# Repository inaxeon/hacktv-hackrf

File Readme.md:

# HackTV "HackDAC"

This repository is a fork of the HackRF project which contains modified firmware and PCB files for the HackDAC.

# What is it?

HackDAC is an add-on board for the HackRF One intended to provide a broadcast quality baseband video and audio output for HackTV. HackDAC was developed to address a number of frustrations of HackTV users and developers. Firstly, the output of the HackRF is quite noisy, to the extent that it’s visible when viewing television signals generated by HackTV. Secondly it is sometimes more desirable to work with baseband video signals, particularly with devices which do not have an RF input.

# Why is it bristling with trimmable inductors? That looks rather dated!

Well yes, it is. For anybody wanting to design a device which has an analogue video output there are certainly more than a few types of chip for the job, however these (to the best of our current knowledge) are all "consumer video encoder" chips. While these devices are plentiful, inexpensive and produce good quality signals using just a single chip with a few passives at the output, unfortunately they do all of the sync generation and chrominance encoding internally, limiting the output typically to just PAL and NTSC (and SECAM in some rare cases).

HackTV on the other hand is a fully software defined TV transmitter which does not want the output hardware doing anything clever for it – this is why it is able to generate a massive range of TV signals, some quite obscure.

Ultimately HackTV wants a high-quality arbitrary video signal generator as its output and sadly there is no commercial reason for such a thing to exist, beyond analogue video test equipment, very little of which is designed or sold today.

In 2022 Danish Entrepreneur Karsten Hansen dumped 4 gigabytes of engineering materials from Philips TV & Test Equipment into a github repository (intellectual property he personally came to own). Contained within the repository was detailed information about how to build and calibrate a very high-quality arbitrary video signal generator circuit first used in the Philips PM5655. This circuit became the basis of "HackDAC Alpha" – the current design.

Unfortunately it's quite difficult to build, and calibrating it takes some practice, not to mention some specialised test equipment. Longer term the project will have to wave goodbye to this circuit and move to a digital oversampling solution however it is important for the time being, firstly because it works and proves the concept, secondly because its performance is exceptional and provides a benchmark for any future designs.

# Firmware details

<details>

Contained within this repository is a modified version of the HackRF One's firmware which is required to support the HackDAC. It is the explicit intention that this firmware must retain all functionality of the HackRF One and full compatibility with libhackrf. As such any defects should be regarded as bugs and reported here.

Note that the HackDAC firmware increases the USB data buffer from 32KiB to the maximum 64KiB. This may effect latency when using the HackRF for low-bandwidth non-HackTV applications.

</details>

# Hardware details

<details>

## Design

The most prominent feature of the present design is the filter after the DAC. It is a full analogue reconstruction filter which corrects its own errors and allows the DAC to run at 1x sample rate. Such a filter is required when attaching to the HackRF as the maximum sample rate is about 20 MHz, not enough even for 2x oversampling.

During operation the HackRF's CPLD is re-programmed to emit data from the normally unused BANK2_AUX header, instead of the on-board analogue frontend. Realisation of video signals is performed by the 16-bit AD768 from Analogue Devices, the very same DAC originally used by Philips. It's an old chip with quite a price tag but remains in production and still has respectable performance even by todays' standards. Replacement of it with a newer, low-cost device was considered however it was found this would impose a number of compromises and require significant alterations to the design, none of which the project is particularly willing to accept at this time. Nonetheless in future it will have to be abandoned due to its high cost.

Video resolution is limited to 15-bit, as the 16th bit from the CPU is used for the Sync output.

Jitter was a particular difficulty during the development of HackDAC. The root cause of the problem is the HackRF's Si5351c/a PLL; a low-quality consumer chip with poor jitter characteristics, even when using the most optimum divisor ratios. To work around the problem, when running in baseband video mode the HackDAC firmware re-programs the Si5351 to act as a clock buffer, disabling its PLL entirely. HackDAC then clocks the Si5351 from its on-board 27 MHz TCXO, providing a stable, extremely low jitter to clock to the HackRF's CPLD and MCU. 

Audio is handled by a PCM5102 DAC run at a sample rate of 210.9 KHz, the 13.5 MHz video sample rate divided by 64. This ratio arises from interleaved transfers of 16KiB video data, followed by 512B of audio data to the HackRF, a scheme which was found to be efficient and reliable.

When a HackDAC is attached to the HackRF it should remain powered down, and not in any way impair non-HackTV related usage of it (even with standard firmware). Any issues in this scenario should be reported as bugs.

## Variable inductor construction

HackDAC uses proprietary Philips inductors in its output filter. Original parts are not purchasable from any source today however they can be recreated using inductor kits. To achieve correct characteristics the following instructions must be exactly followed.

All inductors are made from the WELCO SBK-71S kit *with* the optional SBK-CF1 ferrite cup. Bobbins must be wound with 0.1mm copper wire *using only the bottom half of the bobbon* It is important the top half is left free of windings. Once the bobbins are wound the windings must be varnished to ensure they do not move.

Single winding types:
* 4008 100 09500: 1pcs per board. 42.5 turns. Target inductance: 8.0-15.0uH
* 4008 100 09760: 2pcs per board. 9.5 turns. Target inductance: 0.5-1.0uH
* 4008 100 09750: 3pcs per board. 11.5 turns. Target inductance: 0.8-1.8uH

A single wire is wound counter-clockwise between pins 1 and 4. All turn counts are given including the extra half turn to reach the opposing pin. i.e. 9.5T = 9 full turns from pin 1, plus the extra half turn to reach pin 4.

Double winding types:
* 4008 100 09510: 1pcs per board. 10.5 turns. Target inductance: 0.7-1.2uH
* 4008 100 09770: 1pcs per board. 16.5 turns. Target inductance: 1.3-3.0uH

Two separate wires are wound counter-clockwise (both in the same direction) One starting at pin 1 ending at 4, and another starting at pin 2 ending at 5. Both must be of an identical number of turns. Verification of target inductance must be performed with both windings in parallel.

</details>

# Calibration

<details>

A number of steps are required to calibrate a HackDAC. Below is the method I personally use. I warn that it takes some time to master in practise.

### DC Offset / gain calibration:

Each board has individually calibration DC gain and offset. It is performed using the "hackdac_cal" tool in this repository.

Upon running it with an assembled HackRF/HackDAC the user is given the option to set the output voltage to either -1V, 0V or +1V. Additional keystrokes allow the gain and offset to be adjusted in realtime so to achieve correct voltage as measured on a DMM attached to the HackDAC's video output terminated at 75Ω.

Once the procedure is completed the calibrations can be saved into nonvolatile memory contained within the calibration DAC on the HackDAC board.

### Low pass filter calibration

Test setup:

For this procedure the HackDAC must be connected to a baseband VNA using the A/R MAG input configuration. The procedure is possible with an RF VNA with a built-in S-Parameter test set however the test cable setup will differ and you most likely won't be able to accurately measure frequency response or group delay accurately below 1 MHz.

Firstly the low pass filter must be adjusted:

* L9: 10 MHz
* L8: 8.05 MHz
* L7: 16.8 MHz

Resonant frequencies can be observed in the stopband as per this plot:

### Group delay equaliser calibration

In this procedure the VNA will need to be set the A/R DELAY measurement. L3, L4, L5 and L6 are adjusted to keep Tg deviation within 5ns as per this diagram:

In practise this is rather difficult to do and somewhat overkill for any realistic application today. You may find you can get it within 20ns which is still more than good enough.

### SIN X/X correction calibration

To calibrate the SIN X/X corrector HackTV must be set to generate the SIN X/X test signal. L10 and C39 must be adjusted to achieve symmetry of the SIN X/X test signal as below:

Now start HackTV with the "Pulse & Bar" test signal. Check the 2T pulse is symmetrical as below. Ajust group delay & SIN X/X as necessary to resolve any issues.

### Final check with vectorscope

Lastly if you have an accurate/calibrated vectorscope to hand it is useful for validating the previous adjustments. Start HackTV with the 75% EBU colour bars test signal and verify the output on a vectorscope matches the below:

Colours should fall exactly in the 75% boxes in the graticule, traces between vectors should be perfectly straight. Examples of problems likely to be seen are differential phase errors and incorrect colour subcarrier amplitude. Fine tune the group delay equaliser and SIN X/X correction as necessary to resolve.
</details>

# Specifications

## Video output
* Bandwidth: DC-6 MHz
* Voltage range: 2V pk-pk (+/- 1V)
* Output impedence: 75Ω
* Sample rate: 13.5 MHz (fixed, per CCIR 601)
* Word size: 15-bit

## Sync output
* Output voltage: -1.8V (0v at rest)
* Rise time: 230ns
* Output impedence: 75Ω

## Audio output
* Output voltage: 2.1 V(RMS)
* Sample rate (with video): 210.9 KHz
* Sample rate (standalone): 48 KHz
* Word size: 16-bit

# Schematic

[Can be viewed here](https://github.com/inaxeon/hacktv-hackrf/blob/master/hardware/hackdac-alpha/hackdac-alpha-rev3.pdf).

# How do I obtain one?

While fully open-source HackDACs are produced in small quantities and available to purchase pre-made. Contact me at inaxeon@hotmail.com for more information.

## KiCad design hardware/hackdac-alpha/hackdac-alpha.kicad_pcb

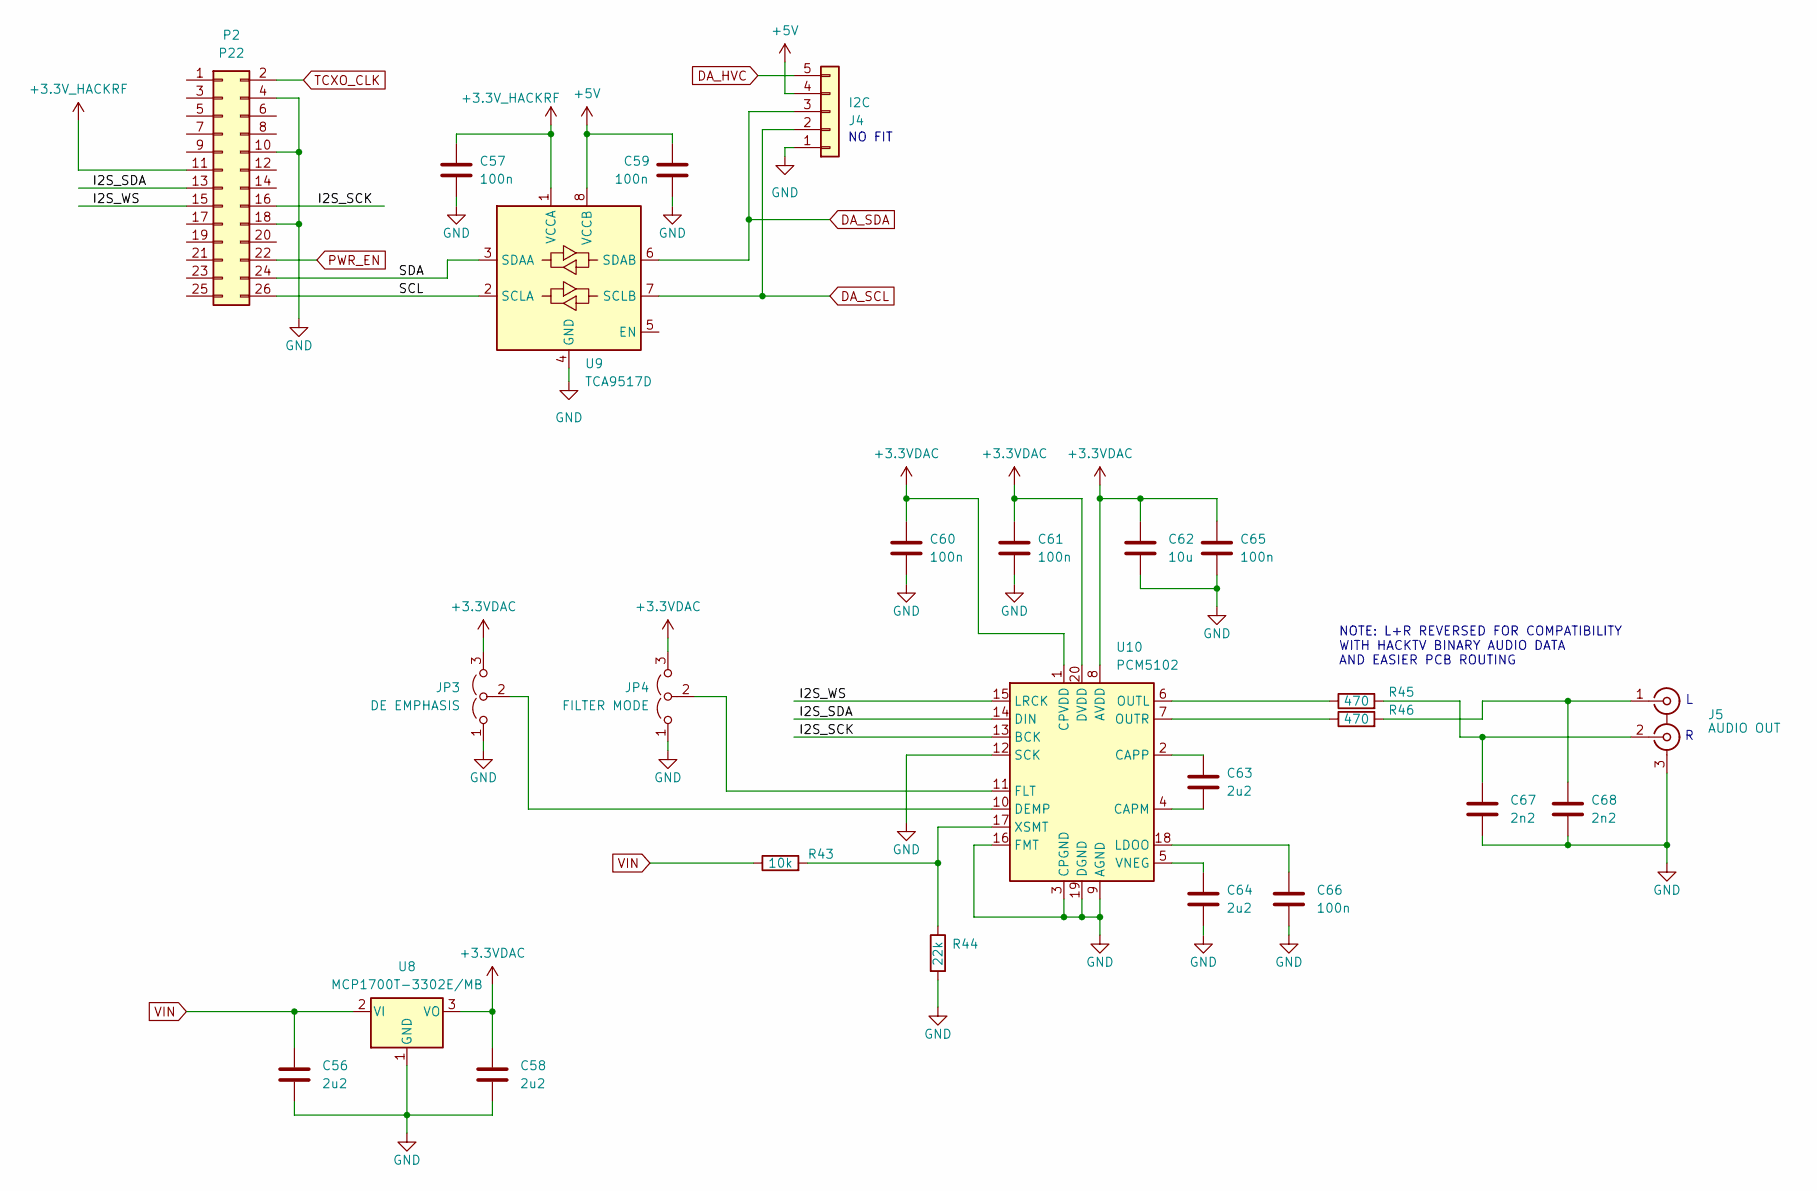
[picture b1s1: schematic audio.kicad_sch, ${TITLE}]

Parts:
C56, C58, C63, C64: 2u2; C_0603_1608Metric
C57, C59, C60, C61, C65, C66: 100n; C_0603_1608Metric
C62: 10u; C_1210_3225Metric
C67, C68: 2n2; C_0603_1608Metric
J4: I2C; Molex_KK-254_AE-6410-05A_1x05_P2.54mm_Vertical
J5: AUDIO OUT; PJRAN2X1U01X
JP3: DE EMPHASIS; SolderJumper-3_P1.3mm_Bridged12_Pad1.0x1.5mm
JP4: FILTER MODE; SolderJumper-3_P1.3mm_Bridged12_Pad1.0x1.5mm
P2: P22; GSG-HEADER-2x13
R43: 10k; R_0603_1608Metric
R44: 22k; R_0603_1608Metric
R45, R46: 470; R_0603_1608Metric
U8: MCP1700T-3302E/MB; SOT-89-3
U9: TCA9517D; SOIC-8_3.9x4.9mm_P1.27mm
U10: PCM5102; TSSOP-20_4.4x6.5mm_P0.65mm

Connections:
+3.3VDAC: C58.1, C60.1, C61.1, C62.1, C65.1, JP3.3 (B), JP4.3 (B), U8.3 (VO), U10.1 (CPVDD), U10.8 (AVDD), U10.20 (DVDD)
+3.3V_HACKRF: C57.1, P2.11, U9.1 (VCCA); also elsewhere on the board
+5V: C59.1, J4.4, U9.8 (VCCB); also elsewhere on the board
/audio/I2S_SCK: P2.16, U10.13 (BCK)
/audio/I2S_SDA: P2.13, U10.14 (DIN)
/audio/I2S_WS: P2.15, U10.15 (LRCK)
/audio/SCL: P2.26, U9.2 (SCLA)
/audio/SDA: P2.24, U9.3 (SDAA)
DA_HVC: J4.5; also elsewhere on the board
DA_SCL: J4.2, U9.7 (SCLB); also elsewhere on the board
DA_SDA: J4.3, U9.6 (SDAB); also elsewhere on the board
GND: C56.2, C57.2, C58.2, C59.2, C60.2, C61.2, C62.2, C64.2, C65.2, C66.2, C67.2, C68.2, J4.1, J5.3 (EXT), JP3.1 (A), JP4.1 (A), P2.4, P2.10, P2.18, R44.2, U8.1 (GND), U9.4 (GND), U10.3 (CPGND), U10.9 (AGND), U10.12 (SCK), U10.16 (FMT), U10.19 (DGND); also elsewhere on the board
unnamed: C68.1, J5.1 (IN1), R46.2
unnamed: C67.1, J5.2 (IN2), R45.2
unnamed: JP3.2 (C), U10.10 (DEMP)
unnamed: JP4.2 (C), U10.11 (FLT)
unnamed: C63.2, U10.4 (CAPM)
unnamed: C63.1, U10.2 (CAPP)
unnamed: C66.1, U10.18 (LDOO)
unnamed: R45.1, U10.6 (OUTL)
unnamed: R46.1, U10.7 (OUTR)
unnamed: C64.1, U10.5 (VNEG)
unnamed: R43.2, R44.1, U10.17 (XSMT)
PWR_EN: P2.22; also elsewhere on the board
TCXO_CLK: P2.2; also elsewhere on the board
VIN: C56.1, R43.1, U8.2 (VI); also elsewhere on the board

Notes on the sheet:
NOTE: L+R REVERSED FOR COMPATIBILITY WITH HACKTV BINARY AUDIO DATA AND EASIER PCB ROUTING
NO FIT

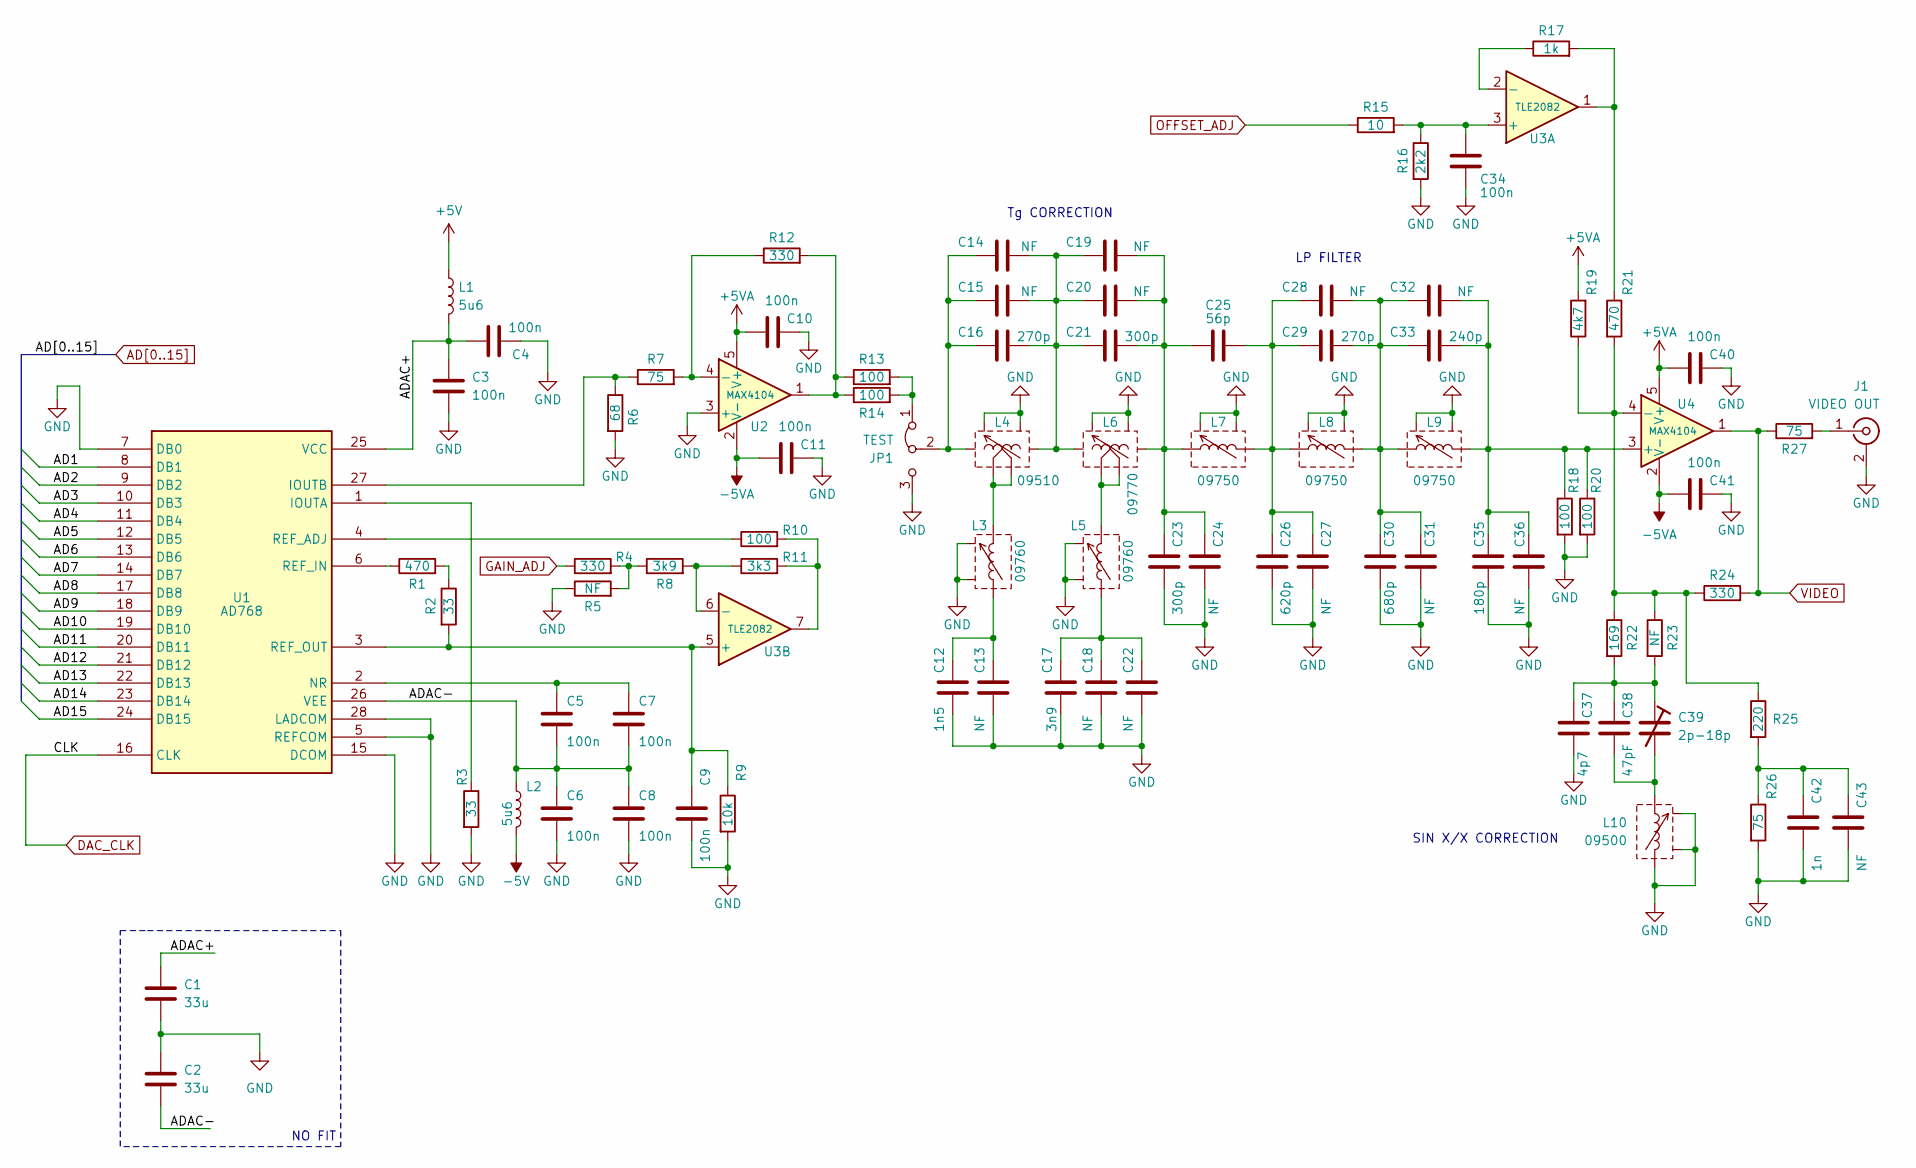
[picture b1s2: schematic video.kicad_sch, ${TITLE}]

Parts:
C1, C2: 33u; C_1210_3225Metric
C3, C4, C5, C6, C7, C8, C9, C10, C11, C34, C40, C41: 100n; C_0603_1608Metric
C12: 1n5; C_0603_1608Metric
C13, C14, C15, C18, C19, C20, C22, C24, C27, C28, C31, C32, C36, C43: NF; C_0603_1608Metric
C16, C29: 270p; C_0603_1608Metric
C17: 3n9; C_0603_1608Metric
C21, C23: 300p; C_0603_1608Metric
C25: 56p; C_0603_1608Metric
C26: 620p; C_0603_1608Metric
C30: 680p; C_0603_1608Metric
C33: 240p; C_0603_1608Metric
C35: 180p; C_0603_1608Metric
C37: 4p7; C_0603_1608Metric
C38: 47pF; C_0603_1608Metric
C39: 2p-18p; BFC2808xxxxx
C42: 1n; C_0603_1608Metric
J1: VIDEO OUT; 731010120
JP1: TEST; PinHeader_1x03_P2.54mm_Vertical
L1, L2: 5u6; L_1210_3225Metric
L3, L5: 09760; NEOSID_7MM
L4: 09510; NEOSID_7MM
L6: 09770; NEOSID_7MM
L7, L8, L9: 09750; NEOSID_7MM
L10: 09500; NEOSID_7MM
R1, R21: 470; R_0603_1608Metric
R2, R3: 33; R_0603_1608Metric
R4, R12, R24: 330; R_0603_1608Metric
R5, R23: NF; R_0603_1608Metric
R6: 68; R_0603_1608Metric
R7, R26, R27: 75; R_0603_1608Metric
R8: 3k9; R_0603_1608Metric
R9: 10k; R_0603_1608Metric
R10, R13, R14, R18, R20: 100; R_0603_1608Metric
R11: 3k3; R_0603_1608Metric
R15: 10; R_0603_1608Metric
R16: 2k2; R_0603_1608Metric
R17: 1k; R_0603_1608Metric
R19: 4k7; R_0603_1608Metric
R22: 169; R_0603_1608Metric
R25: 220; R_0603_1608Metric
U1: AD768; SOIC-28W_7.5x18.7mm_P1.27mm
U2, U4: MAX4104; SOT-23-5
U3: TLE2082; SOIC-8_3.9x4.9mm_P1.27mm

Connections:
+5V: L1.1; also elsewhere on the board
+5VA: C10.1, C40.1, R19.2, U2.5 (V+), U4.5 (V+); also elsewhere on the board
-5V: L2.2; also elsewhere on the board
-5VA: C11.1, C41.1, U2.2 (V-), U4.2 (V-); also elsewhere on the board
/video/ADAC+: C1.1, C3.2, C4.2, L1.2, U1.25 (VCC)
/video/ADAC-: C2.2, C5.2, C6.1, C7.1, C8.1, L2.1, U1.26 (VEE)
AD1: U1.8 (DB1); also elsewhere on the board
AD2: U1.9 (DB2); also elsewhere on the board
AD3: U1.10 (DB3); also elsewhere on the board
AD4: U1.11 (DB4); also elsewhere on the board
AD5: U1.12 (DB5); also elsewhere on the board
AD6: U1.13 (DB6); also elsewhere on the board
AD7: U1.14 (DB7); also elsewhere on the board
AD8: U1.17 (DB8); also elsewhere on the board
AD9: U1.18 (DB9); also elsewhere on the board
AD10: U1.19 (DB10); also elsewhere on the board
AD11: U1.20 (DB11); also elsewhere on the board
AD12: U1.21 (DB12); also elsewhere on the board
AD13: U1.22 (DB13); also elsewhere on the board
AD14: U1.23 (DB14); also elsewhere on the board
AD15: U1.24 (DB15); also elsewhere on the board
DAC_CLK: U1.16 (CLK); also elsewhere on the board
GAIN_ADJ: R4.1; also elsewhere on the board
GND: C1.2, C2.1, C3.1, C4.1, C6.2, C8.2, C9.2, C10.2, C11.2, C12.2, C13.2, C17.2, C18.2, C22.2, C23.2, C24.2, C26.2, C27.2, C30.2, C31.2, C34.2, C35.2, C36.2, C37.2, C40.2, C41.2, C42.2, C43.2, J1.2 (Ext), JP1.3 (B), L3.6, L4.6, L5.6, L6.6, L7.6, L8.6, L9.6, L10.4, L10.6, R3.2, R5.1, R6.2, R9.2, R16.2, R18.2, R20.2, R26.2, U1.5 (REFCOM), U1.7 (DB0), U1.15 (DCOM), U1.28 (LADCOM), U2.3 (+); also elsewhere on the board
unnamed: C12.1, C13.1, L3.4
unnamed: C14.2, C15.2, C16.2, C19.1, C20.1, C21.1, L4.1, L6.5
unnamed: C17.1, C18.1, C22.1, L5.4
unnamed: C19.2, C20.2, C21.2, C23.1, C24.1, C25.1, L6.1, L7.1
unnamed: C25.2, C26.1, C27.1, C28.1, C29.1, L7.4, L8.1
unnamed: C28.2, C29.2, C30.1, C31.1, C32.1, C33.1, L8.4, L9.1
unnamed: C37.1, C38.1, C39.1, R22.2, R23.2
unnamed: C38.2, C39.2, L10.1
unnamed: C42.1, C43.1, R25.2, R26.1
unnamed: J1.1 (In), R27.2
unnamed: JP1.1 (A), R13.2, R14.2
unnamed: C14.1, C15.1, C16.1, JP1.2 (C), L4.5
unnamed: L3.1, L4.2, L4.4
unnamed: L5.1, L6.2, L6.4
unnamed: R1.2, R2.1
unnamed: R4.2, R5.2, R8.1
unnamed: R10.2, R11.2, U3.7
unnamed: R12.2, R13.1, R14.1, U2.1
unnamed: R17.2, R21.1, U3.1
unnamed: R3.1, U1.1 (IOUTA)
unnamed: R6.1, R7.1, U1.27 (IOUTB)
unnamed: C5.1, C7.2, U1.2 (NR)
unnamed: R10.1, U1.4 (REF_ADJ)
unnamed: R1.1, U1.6 (REF_IN)
unnamed: C9.1, R2.2, R9.1, U1.3 (REF_OUT), U3.5 (+)
unnamed: R7.2, R12.1, U2.4 (-)
unnamed: C34.1, R15.2, R16.1, U3.3 (+)
unnamed: R17.1, U3.2 (-)
unnamed: R8.2, R11.1, U3.6 (-)
unnamed: C32.2, C33.2, C35.1, C36.1, L9.4, R18.1, R20.1, U4.3 (+)
unnamed: R19.1, R21.2, R22.1, R23.1, R24.1, R25.1, U4.4 (-)
OFFSET_ADJ: R15.1; also elsewhere on the board
VIDEO: R24.2, R27.1, U4.1; also elsewhere on the board

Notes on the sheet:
LP FILTER
Tg CORRECTION
NO FIT
SIN X/X CORRECTION

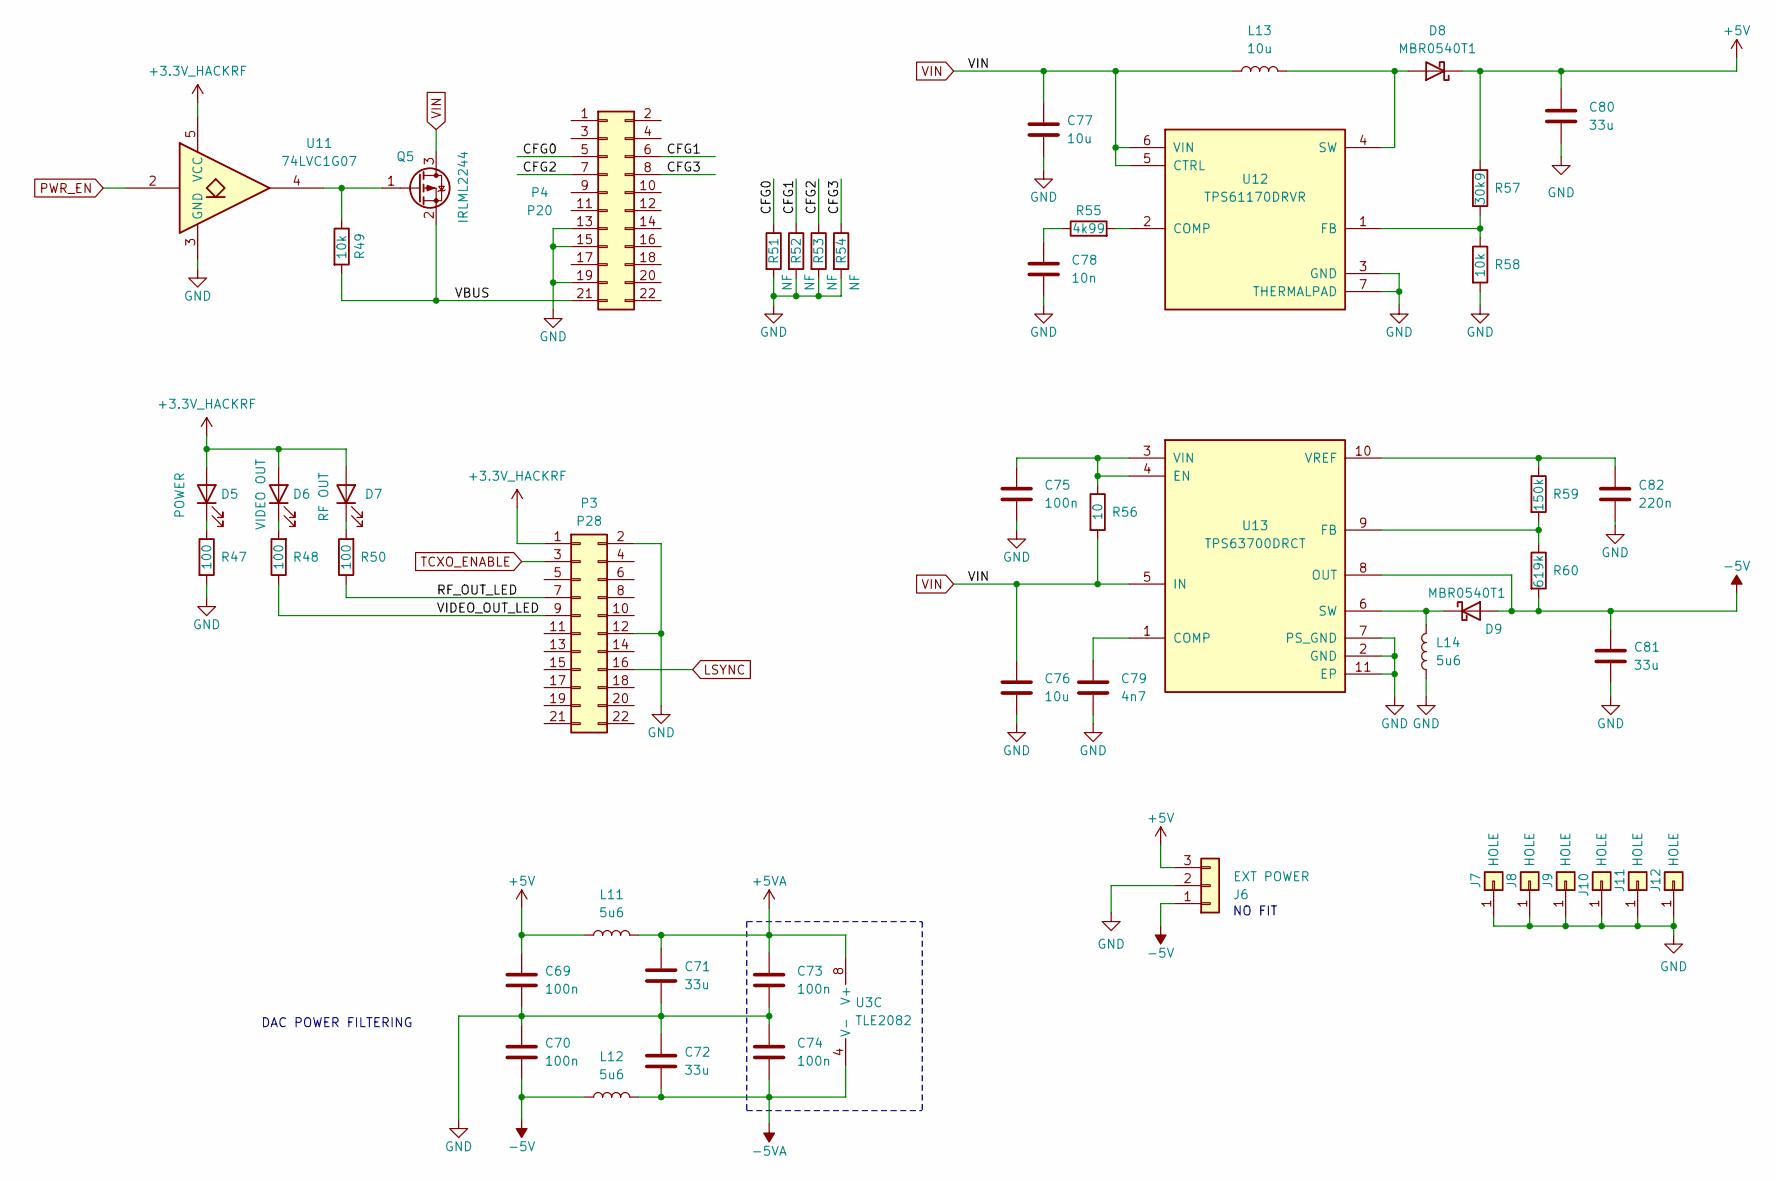
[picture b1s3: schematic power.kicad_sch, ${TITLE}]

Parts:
C69, C70, C73, C74, C75: 100n; C_0603_1608Metric
C71, C72, C80, C81: 33u; C_1210_3225Metric
C76, C77: 10u; C_1210_3225Metric
C78: 10n; C_0603_1608Metric
C79: 4n7; C_0603_1608Metric
C82: 220n; C_0603_1608Metric
D5: POWER; LED_0805_2012Metric
D6: VIDEO OUT; LED_0805_2012Metric
D7: RF OUT; LED_0805_2012Metric
D8, D9: MBR0540T1; D_SOD-123
J6: EXT POWER; Molex_KK-254_AE-6410-03A_1x03_P2.54mm_Vertical
J7, J8, J9, J10, J11, J12: HOLE; GSG-HOLE126MIL-COPPER
L11, L12, L14: 5u6; L_1210_3225Metric
L13: 10u; L_1210_3225Metric
P3: P28; GSG-HEADER-2x11
P4: P20; GSG-HEADER-2x11
Q5: IRLML2244; SOT-23
R47, R48, R50: 100; R_0603_1608Metric
R49, R58: 10k; R_0603_1608Metric
R51, R52, R53, R54: NF; R_0603_1608Metric
R55: 4k99; R_0603_1608Metric
R56: 10; R_0603_1608Metric
R57: 30k9; R_0603_1608Metric
R59: 150k; R_0603_1608Metric
R60: 619k; R_0603_1608Metric
U3: TLE2082; SOIC-8_3.9x4.9mm_P1.27mm
U11: 74LVC1G07; SOT-23-5
U12: TPS61170DRVR; SON65P200X200X80-7N
U13: TPS63700DRCT; VREG_V62_16624-01YE

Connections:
+3.3V_HACKRF: D5.2 (A), D6.2 (A), D7.2 (A), P3.1, U11.5 (VCC); also elsewhere on the board
+5V: C69.1, C80.1, D8.1 (K), J6.3, L11.1, R57.1; also elsewhere on the board
+5VA: C71.1, C73.1, L11.2, U3.8 (V+); also elsewhere on the board
-5V: C70.2, C81.1, D9.2 (A), J6.1, L12.1, R60.2, U13.8 (OUT); also elsewhere on the board
-5VA: C72.2, C74.2, L12.2, U3.4 (V-); also elsewhere on the board
/power/CFG0: P4.5, R51.1
/power/CFG1: P4.6, R52.1
/power/CFG2: P4.7, R53.1
/power/CFG3: P4.8, R54.1
/power/RF_OUT_LED: P3.7, R50.1
/power/VBUS: P4.21, Q5.2 (S), R49.2
/power/VIDEO_OUT_LED: P3.9, R48.1
GND: C69.2, C70.1, C71.2, C72.1, C73.2, C74.1, C75.2, C76.2, C77.2, C78.2, C79.2, C80.2, C81.2, C82.2, J6.2, J7.1, J8.1, J9.1, J10.1, J11.1, J12.1, L14.1, P3.2, P3.12, P4.13, P4.15, P4.19, R47.2, R51.2, R52.2, R53.2, R54.2, R58.2, U11.3 (GND), U12.3 (GND), U12.7 (THERMALPAD), U13.2 (GND), U13.7 (PS_GND), U13.11 (EP); also elsewhere on the board
LSYNC: P3.16; also elsewhere on the board
unnamed: C78.1, R55.1
unnamed: D5.1 (K), R47.1
unnamed: D6.1 (K), R48.2
unnamed: D7.1 (K), R50.2
unnamed: D8.2 (A), L13.2, U12.4 (SW)
unnamed: D9.1 (K), L14.2, U13.6 (SW)
unnamed: Q5.1 (G), R49.1, U11.4
unnamed: R55.2, U12.2 (COMP)
unnamed: R57.2, R58.1, U12.1 (FB)
unnamed: C79.1, U13.1 (COMP)
unnamed: C75.1, R56.1, U13.3 (VIN), U13.4 (EN)
unnamed: R59.2, R60.1, U13.9 (FB)
unnamed: C82.1, R59.1, U13.10 (VREF)
PWR_EN: U11.2; also elsewhere on the board
TCXO_ENABLE: P3.3; also elsewhere on the board
VIN: C76.1, C77.1, L13.1, Q5.3 (D), R56.2, U12.5 (CTRL), U12.6 (VIN), U13.5 (IN); also elsewhere on the board

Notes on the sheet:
NO FIT
DAC POWER FILTERING

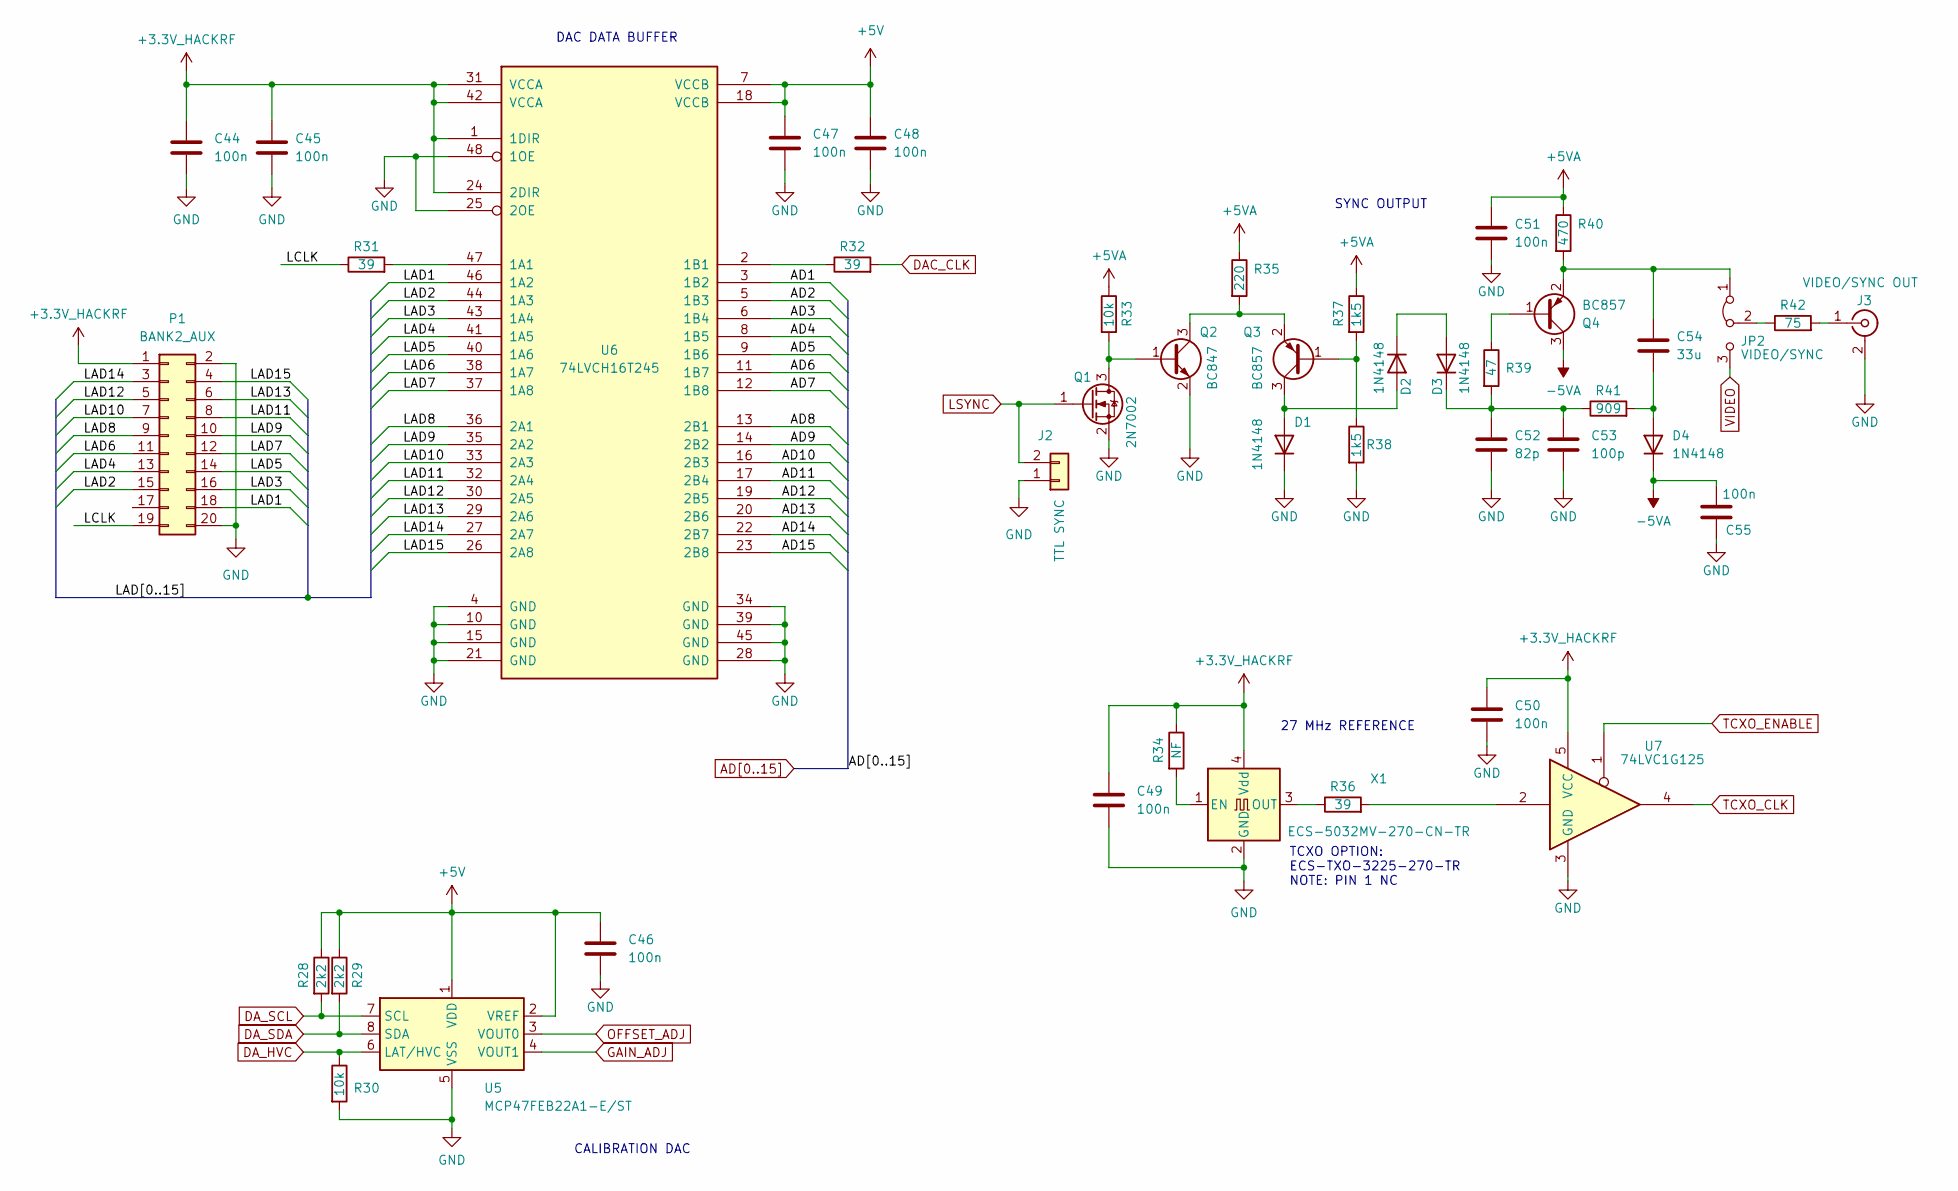
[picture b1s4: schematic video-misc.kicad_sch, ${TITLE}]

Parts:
C44, C45, C46, C47, C48, C49, C50, C51, C55: 100n; C_0603_1608Metric
C52: 82p; C_0603_1608Metric
C53: 100p; C_0603_1608Metric
C54: 33u; C_1210_3225Metric
D1, D2, D3, D4: 1N4148; D_SOD-123
J2: TTL SYNC; Molex_KK-254_AE-6410-02A_1x02_P2.54mm_Vertical
J3: VIDEO/SYNC OUT; 731010120
JP2: VIDEO/SYNC; PinHeader_1x03_P2.54mm_Vertical
P1: BANK2_AUX; GSG-HEADER-2x10
Q1: 2N7002; SOT-23
Q2: BC847; SOT-23
Q3, Q4: BC857; SOT-23
R28, R29: 2k2; R_0603_1608Metric
R30, R33: 10k; R_0603_1608Metric
R31, R32, R36: 39; R_0603_1608Metric
R34: NF; R_0603_1608Metric
R35: 220; R_0603_1608Metric
R37, R38: 1k5; R_0603_1608Metric
R39: 47; R_0603_1608Metric
R40: 470; R_0603_1608Metric
R41: 909; R_0603_1608Metric
R42: 75; R_0603_1608Metric
U5: MCP47FEB22A1-E/ST; TSSOP-8_4.4x3mm_P0.65mm
U6: 74LVCH16T245; SSOP-48_7.5x15.9mm_P0.635mm
U7: 74LVC1G125; SOT-23-5
X1: ECS-5032MV-270-CN-TR; Oscillator_SMD_EuroQuartz_XO53-4Pin_5.0x3.2mm

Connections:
+3.3V_HACKRF: C44.1, C45.1, C49.1, C50.1, P1.1, R34.1, U6.1 (1DIR), U6.24 (2DIR), U6.31 (VCCA), U6.42 (VCCA), U7.5 (VCC), X1.4 (Vdd); also elsewhere on the board
+5V: C46.1, C47.1, C48.1, R28.1, R29.1, U5.1 (VDD), U5.2 (VREF), U6.7 (VCCB), U6.18 (VCCB); also elsewhere on the board
+5VA: C51.1, R33.1, R35.1, R37.1, R40.1; also elsewhere on the board
-5VA: C55.2, D4.1 (K), Q4.3 (C); also elsewhere on the board
/video-misc/LAD1: P1.18, U6.46 (1A2)
/video-misc/LAD2: P1.15, U6.44 (1A3)
/video-misc/LAD3: P1.16, U6.43 (1A4)
/video-misc/LAD4: P1.13, U6.41 (1A5)
/video-misc/LAD5: P1.14, U6.40 (1A6)
/video-misc/LAD6: P1.11, U6.38 (1A7)
/video-misc/LAD7: P1.12, U6.37 (1A8)
/video-misc/LAD8: P1.9, U6.36 (2A1)
/video-misc/LAD9: P1.10, U6.35 (2A2)
/video-misc/LAD10: P1.7, U6.33 (2A3)
/video-misc/LAD11: P1.8, U6.32 (2A4)
/video-misc/LAD12: P1.5, U6.30 (2A5)
/video-misc/LAD13: P1.6, U6.29 (2A6)
/video-misc/LAD14: P1.3, U6.27 (2A7)
/video-misc/LAD15: P1.4, U6.26 (2A8)
/video-misc/LCLK: P1.19, R31.1
AD1: U6.3 (1B2); also elsewhere on the board
AD2: U6.5 (1B3); also elsewhere on the board
AD3: U6.6 (1B4); also elsewhere on the board
AD4: U6.8 (1B5); also elsewhere on the board
AD5: U6.9 (1B6); also elsewhere on the board
AD6: U6.11 (1B7); also elsewhere on the board
AD7: U6.12 (1B8); also elsewhere on the board
AD8: U6.13 (2B1); also elsewhere on the board
AD9: U6.14 (2B2); also elsewhere on the board
AD10: U6.16 (2B3); also elsewhere on the board
AD11: U6.17 (2B4); also elsewhere on the board
AD12: U6.19 (2B5); also elsewhere on the board
AD13: U6.20 (2B6); also elsewhere on the board
AD14: U6.22 (2B7); also elsewhere on the board
AD15: U6.23 (2B8); also elsewhere on the board
DAC_CLK: R32.2; also elsewhere on the board
DA_HVC: R30.1, U5.6 (LAT/HVC); also elsewhere on the board
DA_SCL: R28.2, U5.7 (SCL); also elsewhere on the board
DA_SDA: R29.2, U5.8 (SDA); also elsewhere on the board
GAIN_ADJ: U5.4 (VOUT1); also elsewhere on the board
GND: C44.2, C45.2, C46.2, C47.2, C48.2, C49.2, C50.2, C51.2, C52.2, C53.2, C55.1, D1.1 (K), J2.1, J3.2 (Ext), P1.2, P1.20, Q1.2 (S), Q2.2 (E), R30.2, R38.2, U5.5 (VSS), U6.4 (GND), U6.10 (GND), U6.15 (GND), U6.21 (GND), U6.25 (2OE), U6.28 (GND), U6.34 (GND), U6.39 (GND), U6.45 (GND), U6.48 (1OE), U7.3 (GND), X1.2 (GND); also elsewhere on the board
LSYNC: J2.2, Q1.1 (G); also elsewhere on the board
unnamed: D1.2 (A), D2.2 (A), Q3.3 (C)
unnamed: D2.1 (K), D3.2 (A)
unnamed: C52.1, C53.1, D3.1 (K), R39.2, R41.1
unnamed: C54.2, D4.2 (A), R41.2
unnamed: J3.1 (In), R42.2
unnamed: C54.1, JP2.1 (A), Q4.2 (E), R40.2
unnamed: JP2.2 (C), R42.1
unnamed: Q1.3 (D), Q2.1 (B), R33.2
unnamed: Q2.3 (C), Q3.2 (E), R35.2
unnamed: Q3.1 (B), R37.2, R38.1
unnamed: Q4.1 (B), R39.1
unnamed: R36.2, U7.2
unnamed: R31.2, U6.47 (1A1)
unnamed: R32.1, U6.2 (1B1)
unnamed: R34.2, X1.1 (EN)
unnamed: R36.1, X1.3 (OUT)
OFFSET_ADJ: U5.3 (VOUT0); also elsewhere on the board
TCXO_CLK: U7.4; also elsewhere on the board
TCXO_ENABLE: U7.1; also elsewhere on the board
VIDEO: JP2.3 (B); also elsewhere on the board

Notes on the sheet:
CALIBRATION DAC
DAC DATA BUFFER
TCXO OPTION: ECS-TXO-3225-270-TR NOTE: PIN 1 NC
27 MHz REFERENCE
SYNC OUTPUT

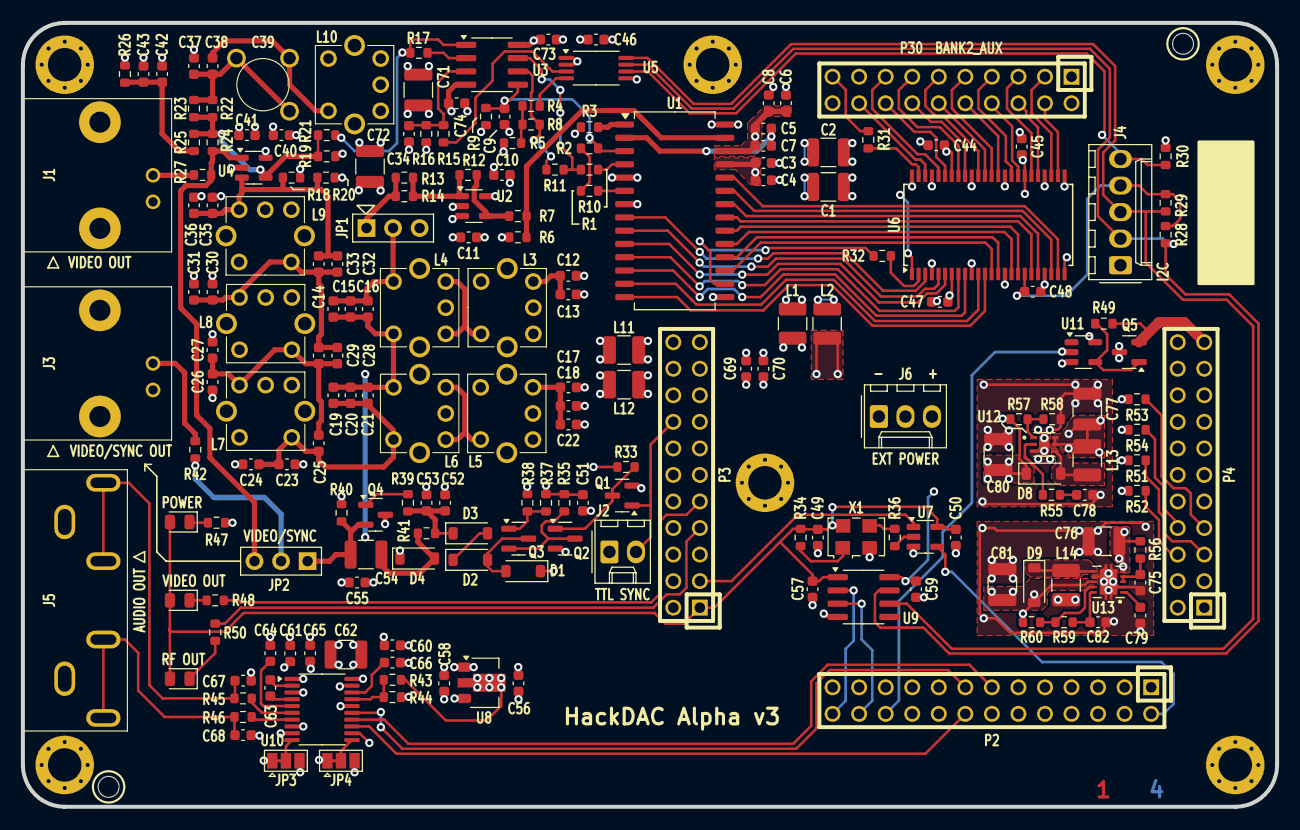
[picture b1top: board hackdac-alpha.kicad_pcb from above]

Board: 4 copper layers, 120.0 x 75.0 mm, 206 parts (0 on the bottom side), 135 nets.

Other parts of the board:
FID1, FID2: FIDUCIAL; GSG-MARK1MM

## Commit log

2024-10-02 HackDAC CPLD changes
2024-10-04 Now actually working
2024-10-06 Outputs at 0V at idle
2024-10-07 Modified to use on-board TCXO
2024-10-07 Removed unused signal
2024-10-07 SGPIO changes
2024-10-07 Moved SGPIO clock to SGPIO14 so that the R9 will also work
2024-11-06 fixed clock phase issue reported by fsphil
2024-11-06 Invert sync polarity for v2 board
2024-11-06 Add Video out LED
2024-11-09 audio PoC
2024-11-09 Fixed merge conflict
2024-11-11 audio WIP
2024-11-21 Audio now pretty much good
2024-11-21 Video LED only on in baseband mode
2024-11-21 I2S buffer sizing tidy-up
2024-11-22 Block TCXO mode in RF mode
2024-11-22 Move hackdac configuration away from bit 0 (used for HW sync)
2024-11-22 mask hackdac bits out of hw_sync mode
2024-11-23 Add PCB design files for V2 alpha board
2024-11-24 Add missing component values
2024-11-26 Add beginnings of DC calibration tool
2024-11-26 DC calibration tool WIP
2024-11-27 2's compliment in CPLD
2024-11-27 Fix lsb data error
2024-11-27 Update component values
2024-11-27 Removed incorrect comment
2024-11-29 Big refactor after original approach to audio clocks was found to be a fail on non-R9 boards. baseband mode now requires a 27 MHz clkin
2024-12-03 Zero video output when running in RF mode. Various other small clean-ups
2024-12-07 Various fixes after running up V2 boards
2024-12-07 Update with V2 mods
2024-12-08 Fixed issue where audio is occasionally crackly after resuming from buffer underrun
2024-12-09 Final values for V2 board
2024-12-09 More specs
2024-12-09 typo
2024-12-09 Schematic link
2024-12-09 Add word sizes to spec
2024-12-10 Simplify
2024-12-22 Fixed build error. Moved i2s startup so that counters are properly initialised
2024-12-28 Beginnings of V3 - re-evalulate filter
2024-12-29 More V3 component rationalisation
2024-12-30 Last of major V3 changes
2024-12-31 V3 PCB WIP
2025-01-01 V3 layout mostly complete
2025-01-01 Optional caps for DAC supply
2025-01-10 More PCB layout for V3, update readme
2025-01-10 Inductor build info
2025-01-10 Added cal info
2025-01-10 Details sections
2025-01-10 More details sections
2025-01-10 Filter explanation
2025-01-10 Whitespace
2025-01-13 V3 firmware changes
2025-01-13 Modify I2C buffering to allow power-down of HackDAC
2025-01-16 Tidy up i2s context
2025-01-16 Move LEDs underneath lightpipes
2025-01-25 Changed X1 to 5x3.2mm footprint
2025-01-26 Add jumper to configure sync out connector
2025-01-27 Added configuration straps
2025-01-27 V3 tid-ups
2025-01-28 Final V3 board
2025-02-14 Fixed a couple of incorrect component values
2025-03-04 Fix mistake in tuning procedure
2025-03-06 Fixed audio DMA conflict problem. Added V3 board power-up soft-start
2025-03-07 Rationalise I2S counters. Add board ID code.
2025-03-19 Add V3 schematic
2025-03-24 hackdac-cal now working on Windows
2025-03-24 Fixed arrow keys on windows
2025-03-24 Add V3 image
2025-03-27 Add firmware release

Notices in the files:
parts and their libraries:
COPYRIGHT: Copyright 2024 Matt Millman
LICENSE: Licensed under the CERN-OHL-P v2
